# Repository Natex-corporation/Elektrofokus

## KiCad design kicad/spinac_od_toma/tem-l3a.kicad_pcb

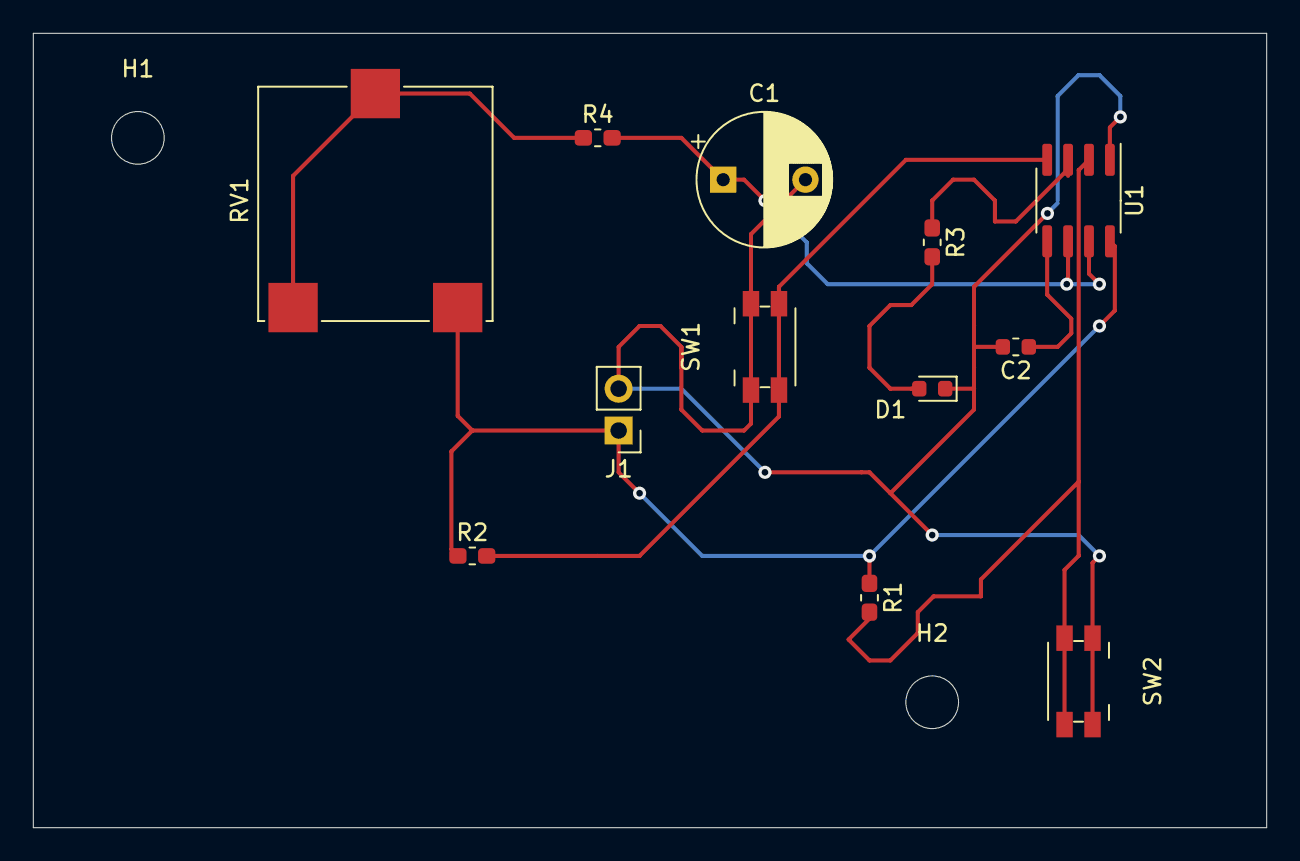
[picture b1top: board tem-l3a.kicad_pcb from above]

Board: 2 copper layers, 74.9 x 48.3 mm, 14 parts (0 on the bottom side), 9 nets.

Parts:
C1: 100uF; CP_Radial_D8.0mm_P5.00mm
C2: 100nF; C_0603_1608Metric
D1: LED; LED_0603_1608Metric
H1, H2: MountingHole; MountingHole_3.2mm_M3
J1: Conn_01x02_Male; PinHeader_1x02_P2.54mm_Vertical
R1, R2, R4: 10k; R_0603_1608Metric_Pad1.05x0.95mm_HandSolder
R3: 470; R_0603_1608Metric_Pad1.05x0.95mm_HandSolder
RV1: 1M; Potentiometer_ACP_CA14-VSMD_Vertical
SW1, SW2: SW_Push; Panasonic_EVQPUJ_EVQPUA
U1: LM555xM; SOIC-8_3.9x4.9mm_P1.27mm

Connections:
unnamed: C1.1, R4.2, U1.6, U1.7
unnamed: C1.2, C2.2, D1.1, J1.2, SW1.1, SW2.1, U1.1
unnamed: C2.1, U1.5
unnamed: D1.2, R3.2
unnamed: J1.1, R1.1, R2.1, RV1.1, U1.8
unnamed: R1.2, SW2.2, U1.2
unnamed: R2.2, SW1.2, U1.4
unnamed: R3.1, U1.3
unnamed: R4.1, RV1.2, RV1.3

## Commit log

2021-11-09 all the files
    the upload of all of the files
2021-11-10 kicad
2021-11-17 KiCAD - 1. projekt od DAVIDA
    chybi jen vyvody pro baterku, nebo neco takoveho, uz si to presne nepamatuju
2021-11-24 vývody
2021-11-24 tomova složka
2021-11-24 24.11-Dejv
2021-11-27 Updated Toms file
2021-12-02 1.prosinec
2021-12-08 měření oscilátoru
2022-01-04 added rc2000 mesuraments
2022-01-26 updated to kicad6.0.1.
2022-03-22 added scripts for graph generation
2022-09-22 mereni transformataru
    Transformatory 4.rocnik
2022-09-22 Pridani protokolu
2022-09-29 vyřešeno
    výsledky pro transformátory
2022-10-03 abraka dabraka
2022-10-03 small update
2022-10-03 přidání protokolu z transformátorů
2022-11-02 přidaní dalších protokolů, které jsem někde našel
2023-01-19 tom zapomíná nahrávat
2023-01-19 neco se stalo a ted mam o soubor navic lul
2023-01-19 Protokol klopne obvody
    ale z nejakyho duvodu tomu rikam plc tak tezko rict :sweat_smile:
2023-01-26 je potreba upravit jeste i velikost pisma
2023-01-27 PLC oprava, ale fotky tam furt zustali
2023-03-01 added protocol from esp 32
2023-03-02 propusti
    naměřené hodnoty pro propusti
2023-03-02 clean up
    removed propusti duplicate, generated graph with x nad y lables
2023-03-02 Add protocol Filtery, add gitignore for latex files
2023-03-03 Update hodnoty.xlsx
    lol nějká změna s daty
2023-03-04 propuste oprava plotovani
    zesileni misto absoltni hodnoty napeti
2023-03-05 add function fit to propuste
2023-03-23 tom opravoval grafy
    jsou přidány i polární grafy kdyby někdo chtěl
2023-03-23 Adding second graph to propuste
